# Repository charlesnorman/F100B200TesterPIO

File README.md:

# F100B200TesterPIO
F100B200 tester using Platformio

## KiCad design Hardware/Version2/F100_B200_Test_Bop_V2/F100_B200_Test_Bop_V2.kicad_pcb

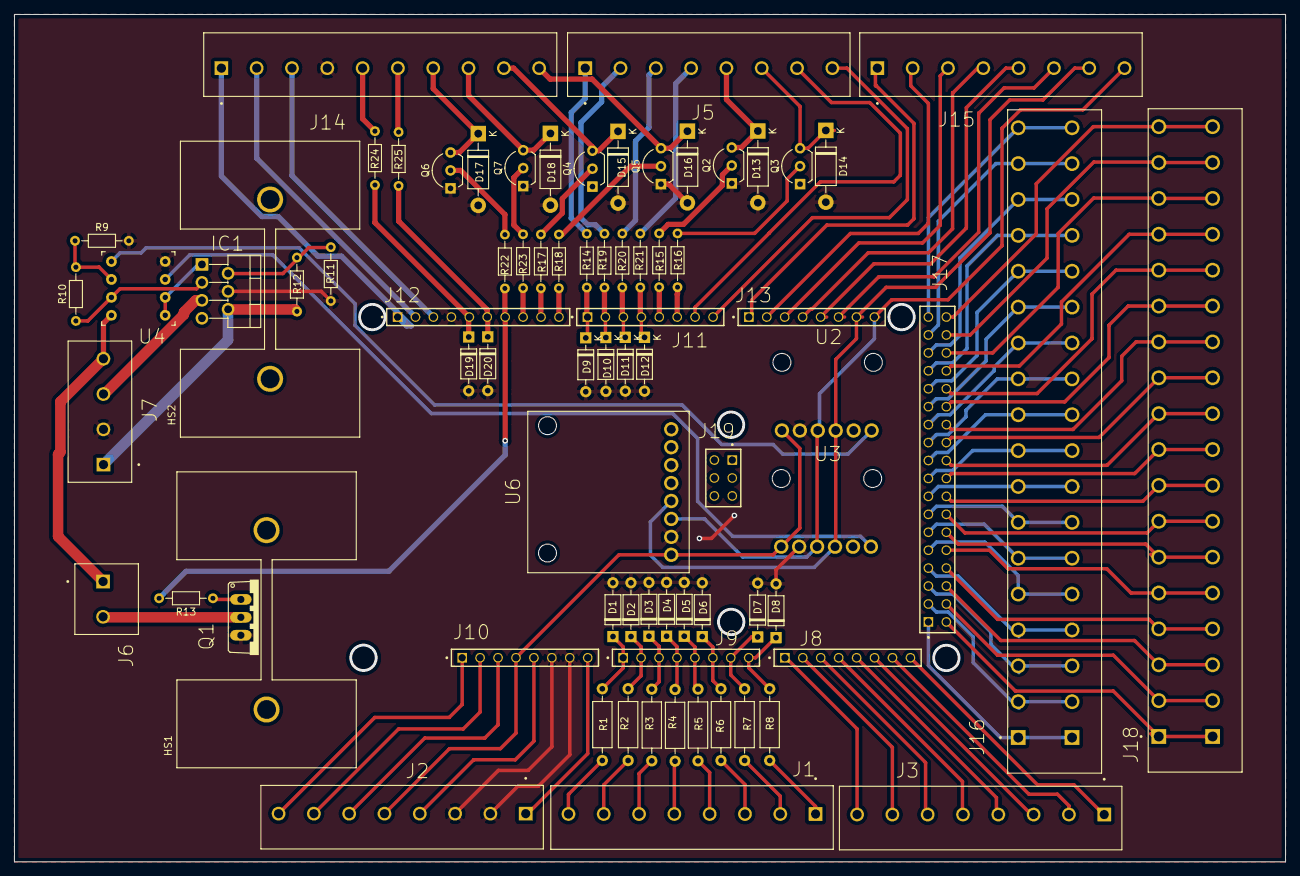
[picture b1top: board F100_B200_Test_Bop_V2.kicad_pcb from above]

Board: 2 copper layers, 180.0 x 120.0 mm, 77 parts (0 on the bottom side), 121 nets.

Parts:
D1, D2, D3, D4, D5, D6, D7, D8, D9, D10, D11, D12, D19, D20: D_Zener; D_DO-35_SOD27_P7.62mm_Horizontal
D13, D14, D15, D16, D17, D18: 1N4004-TP; D_DO-41_SOD81_P10.16mm_Horizontal
HS1, HS2: Heatsink; HSINK_529802B02500G
IC1: OPA548T; TO-220-7_P2.54x3.7mm_StaggerOdd_Lead3.8mm_Vertical
J1, J2, J3, J5, J15: Screw_Terminal_01x08; CUI_TB001-500-08BE
J6: Screw_Terminal_01x02; CUI_TB001-500-02BE
J7: Screw_Terminal_01x04; CUI_TB001-500-04BE
J8, J9, J10, J11, J13: ESQ-108-14-T-S; SAMTEC_ESQ-108-14-T-S
J12: ESQ-110-14-T-S; SAMTEC_ESQ-110-14-T-S
J14: TB001-500-10BE; CUI_TB001-500-10BE
J16, J18: 102-TBL004V-508-18BE-2GY-ND; CUI_TBL004V-508-18BE-2GY
J17: ESQ-118-14-G-D; SAMTEC_ESQ-118-14-G-D
J19: ESQ-103-14-G-D; SAMTEC_ESQ-103-14-G-D
Q1: FQP30N06L; TO220V
Q2, Q3, Q4, Q5, Q6, Q7: Q_NPN_EBC; TO-92L_Inline_Wide
R1, R2, R3, R4, R5, R6, R7, R8: 10k; R_Axial_DIN0207_L6.3mm_D2.5mm_P10.16mm_Horizontal
R9: 20k; R_Axial_DIN0204_L3.6mm_D1.6mm_P7.62mm_Horizontal
R10, R12, R14, R19, R20, R21, R24, R25: 10k; R_Axial_DIN0204_L3.6mm_D1.6mm_P7.62mm_Horizontal
R11: 1.21k; R_Axial_DIN0204_L3.6mm_D1.6mm_P7.62mm_Horizontal
R13, R15, R16, R17, R18, R22, R23: 2.7k; R_Axial_DIN0204_L3.6mm_D1.6mm_P7.62mm_Horizontal
U2, U3: MCP4725; Adafruit-MCP4725
U4: LMC662; SOCKET_DIP-8_7.62mm_Conn
U6: INA260; Adafruit_INA260

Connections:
/12VDC: J6.1, J7.4, U4.8
/24VDC: IC1.5, J7.3
/+3V3: J2.5, J10.04, U2.VDD, U3.VDD, U6.VCC
/+5V: J2.4, J10.05
/A0: D1.1, J9.01, R1.2
/A1: D2.1, J9.02, R2.2
/A2: D3.1, J9.03, R3.2
/A3: D4.1, J9.04, R4.2
/A4: D5.1, J9.05, R5.2
/A5: D6.1, J9.06, R6.2
/A6: D7.1, J9.07, R7.2
/A7: D8.1, J9.08, R8.2
/A8: J3.8, J8.01
/A9: J3.7, J8.02
/A10: J3.6, J8.03
/A11: J3.5, J8.04
/AREF: J12.03, J14.3
/BatSimulator: IC1.6, J7.1, R12.1
/CANR: J3.2, J8.07
/CANT: J3.1, J8.08
/D0: J5.8, J11.08
/D1: J5.7, J11.07
/D2: J11.06, R16.2
/D3: J11.05, R15.2
/D4: D12.1, J11.04, R21.2
/D5: D11.1, J11.03, R20.2
/D6: D10.1, J11.02, R19.2
/D7: D9.1, J11.01, R14.2
/D8: J12.10, R18.2
/D9: J12.09, R17.2
/D10: J12.08, R23.2
/D11: J12.07, R13.2, R22.2
/D12: D20.1, J12.06, R25.2
/D13: D19.1, J12.05, R24.2
/D14: J13.01, J15.1
/D15: J13.02, J15.2
/D16: J13.03, J15.3
/D17: J13.04, J15.4
/D18: J13.05, J15.5
/D19: J13.06, J15.6
/D20: J13.07, J15.7, U2.SDA, U3.SDA, U6.SDA
/D21: J13.08, J15.8, U2.SCL, U3.SCL, U6.SCL
/DAC0: J3.4, J8.05
/DAC1: J3.3, J8.06
/IOREF: J2.7, J10.02
/NC: J2.8, J10.01
/RESET: J2.6, J10.03
/SCL1: J12.01, J14.1
/SDA1: J12.02, J14.2
/VIN: J2.1, J10.08
GND: D1.2, D2.2, D3.2, D4.2, D5.2, D6.2, D7.2, D8.2, D9.2, D10.2, D11.2, D12.2, D13.2, D14.2, D15.2, D16.2, D17.2, D18.2, D19.2, D20.2, IC1.4, J2.2, J2.3, J7.2, J10.06, J10.07, J12.04, J14.4, Q1.3, Q2.1, Q3.1, Q4.1, Q5.1, Q6.1, Q7.1, R9.2, R11.2, U2.GND, U3.GND, U4.4, U6.GND
unnamed: D13.1, J5.5, Q2.3
unnamed: D14.1, J5.6, Q3.3
unnamed: D15.1, J14.9, Q4.3
unnamed: D16.1, J14.10, Q5.3
unnamed: D17.1, J14.7, Q6.3
unnamed: D18.1, J14.8, Q7.3
unnamed: IC1.1, U4.1, U4.2
unnamed: IC1.2, R11.1, R12.2
unnamed: IC1.3, R10.1, U4.7
unnamed: J1.1, R8.1
unnamed: J1.2, R7.1
unnamed: J1.3, R6.1
unnamed: J1.4, R5.1
unnamed: J1.5, R4.1
unnamed: J1.6, R3.1
unnamed: J1.7, R2.1
unnamed: J1.8, R1.1
unnamed: J5.1, R14.1
unnamed: J5.2, R19.1
unnamed: J5.3, R20.1
unnamed: J5.4, R21.1
unnamed: J6.2, Q1.2
unnamed: J14.5, R24.1
unnamed: J14.6, R25.1
unnamed: J16.1, J17.01
unnamed: J16.2, J17.03
unnamed: J16.3, J17.05
unnamed: J16.4, J17.07
unnamed: J16.5, J17.09
unnamed: J16.6, J17.11
unnamed: J16.7, J17.13
unnamed: J16.8, J17.15
unnamed: J16.9, J17.17
unnamed: J16.10, J17.19
unnamed: J16.11, J17.21
unnamed: J16.12, J17.23
unnamed: J16.13, J17.25
unnamed: J16.14, J17.27
unnamed: J16.15, J17.29
unnamed: J16.16, J17.31
unnamed: J16.17, J17.33
unnamed: J16.18, J17.35
unnamed: J17.02, J18.1
unnamed: J17.04, J18.2
unnamed: J17.06, J18.3
unnamed: J17.08, J18.4
unnamed: J17.10, J18.5
unnamed: J17.12, J18.6
unnamed: J17.14, J18.7
unnamed: J17.16, J18.8
unnamed: J17.18, J18.9
unnamed: J17.20, J18.10
unnamed: J17.22, J18.11
unnamed: J17.24, J18.12
unnamed: J17.26, J18.13
unnamed: J17.28, J18.14
unnamed: J17.30, J18.15
unnamed: J17.32, J18.16
unnamed: J17.34, J18.17
unnamed: J17.36, J18.18
unnamed: Q1.1, R13.1
unnamed: Q2.2, R15.1
unnamed: Q3.2, R16.1
unnamed: Q4.2, R17.1
unnamed: Q5.2, R18.1
unnamed: Q6.2, R22.1
unnamed: Q7.2, R23.1
unnamed: R9.1, R10.2, U4.6
unnamed: U2.VOUT, U4.5
unnamed: U3.VOUT, U4.3

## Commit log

2020-11-08 Original import
2020-11-10 added relay drive logic
2020-11-12 added Serial USB
2020-11-23 Fixing bugs and working in board new file: .vscode/tasks.json modified: lib/Adafruit_INA260_Library/Adafruit_INA260.cpp modified: lib/PushButtonController/PushButtonController.cpp modified: lib/PushB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
2020-11-24 From work
2020-11-26 getting ready to merge
2020-11-26 json coms added with python test program new file: .vscode/settings.json new file: coms_python.py modified: src/F100B200Tester.cpp modified: src/notes.txt
2020-11-29 Serial coms working modified: .vscode/settings.json new file: GUI.py new file: __pycache__/GUI.cpython-37.pyc new file: __pycache__/test.cpython-39.pyc modified: coms_python.py modified: src/F100B200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
2020-11-29 Worked on conrtrol of due from python modified: coms_python.py modified: src/F100B200Tester.cpp
2020-11-29 First operational prototype - no auto modified: coms_python.py modified: src/F100B200Tester.cpp
2020-11-30 refactore Python, moved gui to own file deleted: GUI.py new file: __pycache__/gui_layout.cpython-39.pyc modified: coms_python.py new file: gui_layout.py deleted: test.py
2020-12-01 Work on gui modified: coms_python.py new file: test.py
2020-12-02 Added simulator
2020-12-02 Added code folding to python, fixed bug in update of radio buttons modified: .vscode/settings.json modified: __pycache__/gui_layout.cpython-39.pyc modified: coms_python.py modified: gui_layout.py
2020-12-02 Added tabs to gui
2020-12-03 worked on gui
2020-12-03 Work on manual tab
2020-12-04 Work on Man tab
2020-12-09 Imported hardware folder
2020-12-13 modified: __pycache__/gui_layout.cpython-39.pyc modified: gui_layout.py
2020-12-14 "change voltage control to PID"
2020-12-24 Added TM1638 Displays
2020-12-24 Added TM1637 Displays new file: Hardware/Version2/Documents/Serial7SegmentDisplay
2021-01-09 Work on GUI
2021-02-11 clean up
2021-02-23 added mechanical dwgs
2021-04-03 changed to tkinter build with page changed to python venv
